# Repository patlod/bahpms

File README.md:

# bahpms

Thesis Project:  Development and Evaluation of a Hybrid Power Management System for Airships Intended for Infrared Thermographic Inspection of Photovoltaic Plants

## Airship Prototype

## Concept

### Inteded Mission
While vehcile monitors photovoltaic plants it will extend its flight time by charging itself with solar power.

## Gondola & Vehicle Control

## Hybrid Power Management System (HPMS)
Hardware which manages the charging process of the vehicle and switching between power supplies.

## Testing HPMS

## Hardware Communication Client on the Ground
### Concept

Wireless data exchange with vehicle hardware including charge states, charge rates, battery information (which is currently active and which is charged), manually switch between power supplies, etc.

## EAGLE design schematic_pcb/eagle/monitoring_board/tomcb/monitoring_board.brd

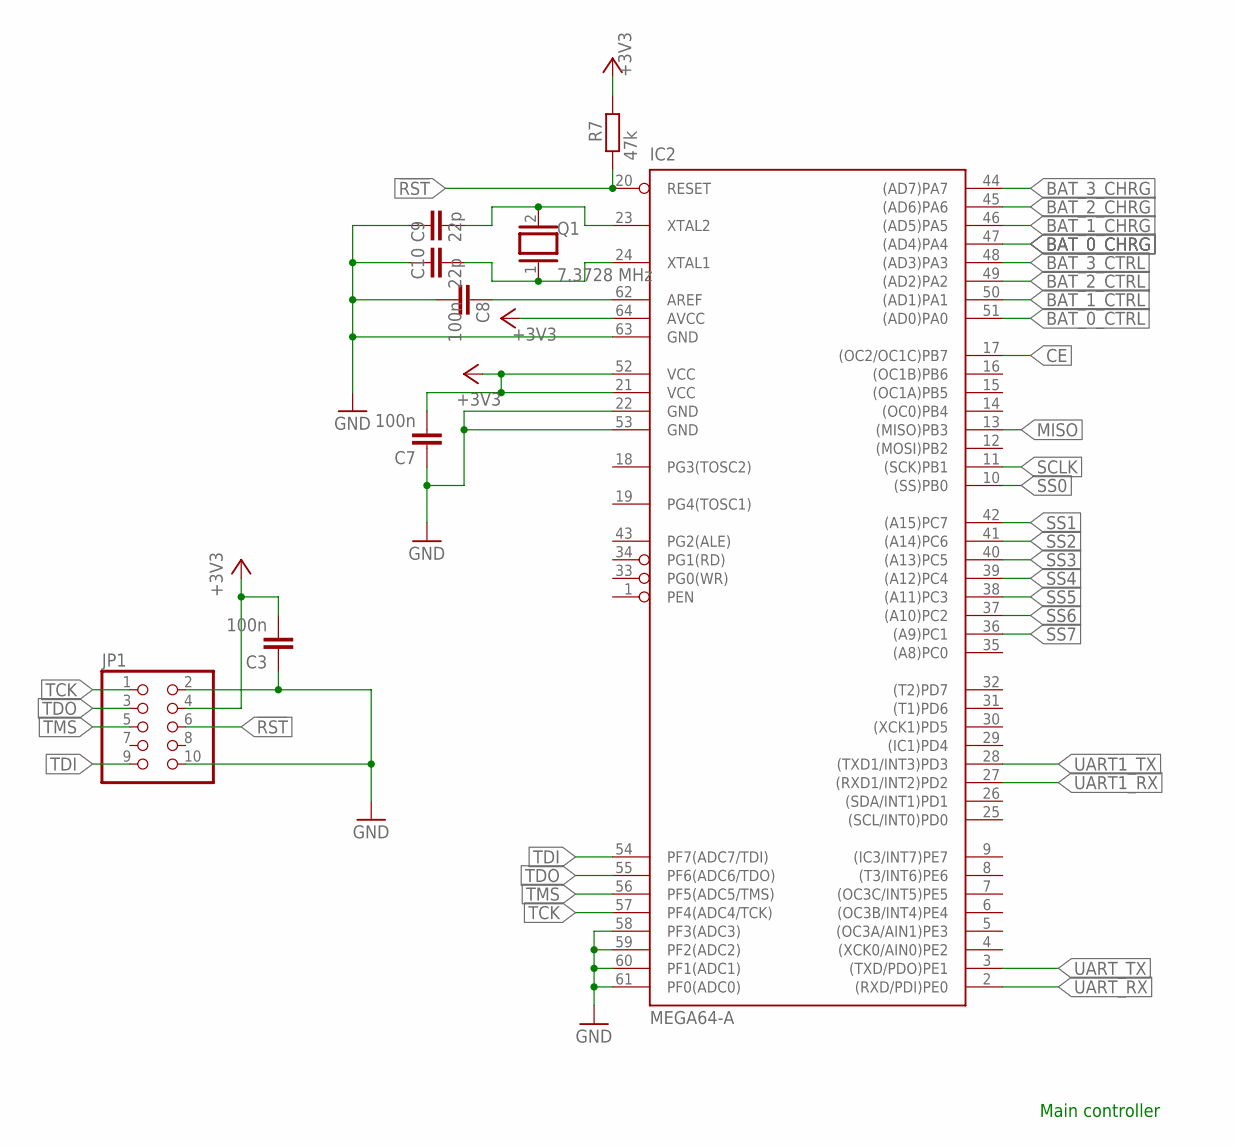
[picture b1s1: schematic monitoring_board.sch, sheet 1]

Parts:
C3, C7, C8: 100n; C0603
C9, C10: 22p; C0603
IC2: MEGA64-A; TQFP64
JP1: PINHD-2X5; 2X05
Q1: 7.3728 MHz; QS
R7: 47k; R0603

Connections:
!RST: IC2.20 (RESET), JP1.6, R7.1
AREF: C8.1, IC2.62 (AREF)
BAT_0_CHRG: IC2.47 ((AD4)PA4); also elsewhere on the board
BAT_0_CTRL: IC2.51 ((AD0)PA0); also elsewhere on the board
BAT_1_CHRG: IC2.46 ((AD5)PA5); also elsewhere on the board
BAT_1_CTRL: IC2.50 ((AD1)PA1); also elsewhere on the board
BAT_2_CHRG: IC2.45 ((AD6)PA6); also elsewhere on the board
BAT_2_CTRL: IC2.49 ((AD2)PA2); also elsewhere on the board
BAT_3_CHRG: IC2.44 ((AD7)PA7); also elsewhere on the board
BAT_3_CTRL: IC2.48 ((AD3)PA3); also elsewhere on the board
CE: IC2.17 ((OC2/OC1C)PB7); also elsewhere on the board
GND: C3.1, C7.1, C8.2, C9.1, C10.1, IC2.22 (GND), IC2.53 (GND), IC2.58 (PF3(ADC3)), IC2.59 (PF2(ADC2)), IC2.60 (PF1(ADC1)), IC2.61 (PF0(ADC0)), IC2.63 (GND), JP1.2, JP1.10; also elsewhere on the board
MISO: IC2.13 ((MISO)PB3); also elsewhere on the board
unnamed: C9.2, IC2.23 (XTAL2), Q1.2
unnamed: C10.2, IC2.24 (XTAL1), Q1.1
SCLK: IC2.11 ((SCK)PB1); also elsewhere on the board
SS0: IC2.10 ((SS)PB0); also elsewhere on the board
SS1: IC2.42 ((A15)PC7); also elsewhere on the board
SS2: IC2.41 ((A14)PC6); also elsewhere on the board
SS3: IC2.40 ((A13)PC5); also elsewhere on the board
SS4: IC2.39 ((A12)PC4); also elsewhere on the board
SS5: IC2.38 ((A11)PC3); also elsewhere on the board
SS6: IC2.37 ((A10)PC2); also elsewhere on the board
SS7: IC2.36 ((A9)PC1); also elsewhere on the board
TCK: IC2.57 (PF4(ADC4/TCK)), JP1.1
TDI: IC2.54 (PF7(ADC7/TDI)), JP1.9
TDO: IC2.55 (PF6(ADC6/TDO)), JP1.3
TMS: IC2.56 (PF5(ADC5/TMS)), JP1.5
UART1_RX: IC2.27 ((RXD1/INT2)PD2); also elsewhere on the board
UART1_TX: IC2.28 ((TXD1/INT3)PD3); also elsewhere on the board
UART_RX: IC2.2 ((RXD/PDI)PE0); also elsewhere on the board
UART_TX: IC2.3 ((TXD/PDO)PE1); also elsewhere on the board
VCC3V3: C3.2, C7.2, IC2.21 (VCC), IC2.52 (VCC), IC2.64 (AVCC), JP1.4, R7.2; also elsewhere on the board

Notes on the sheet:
Main controller

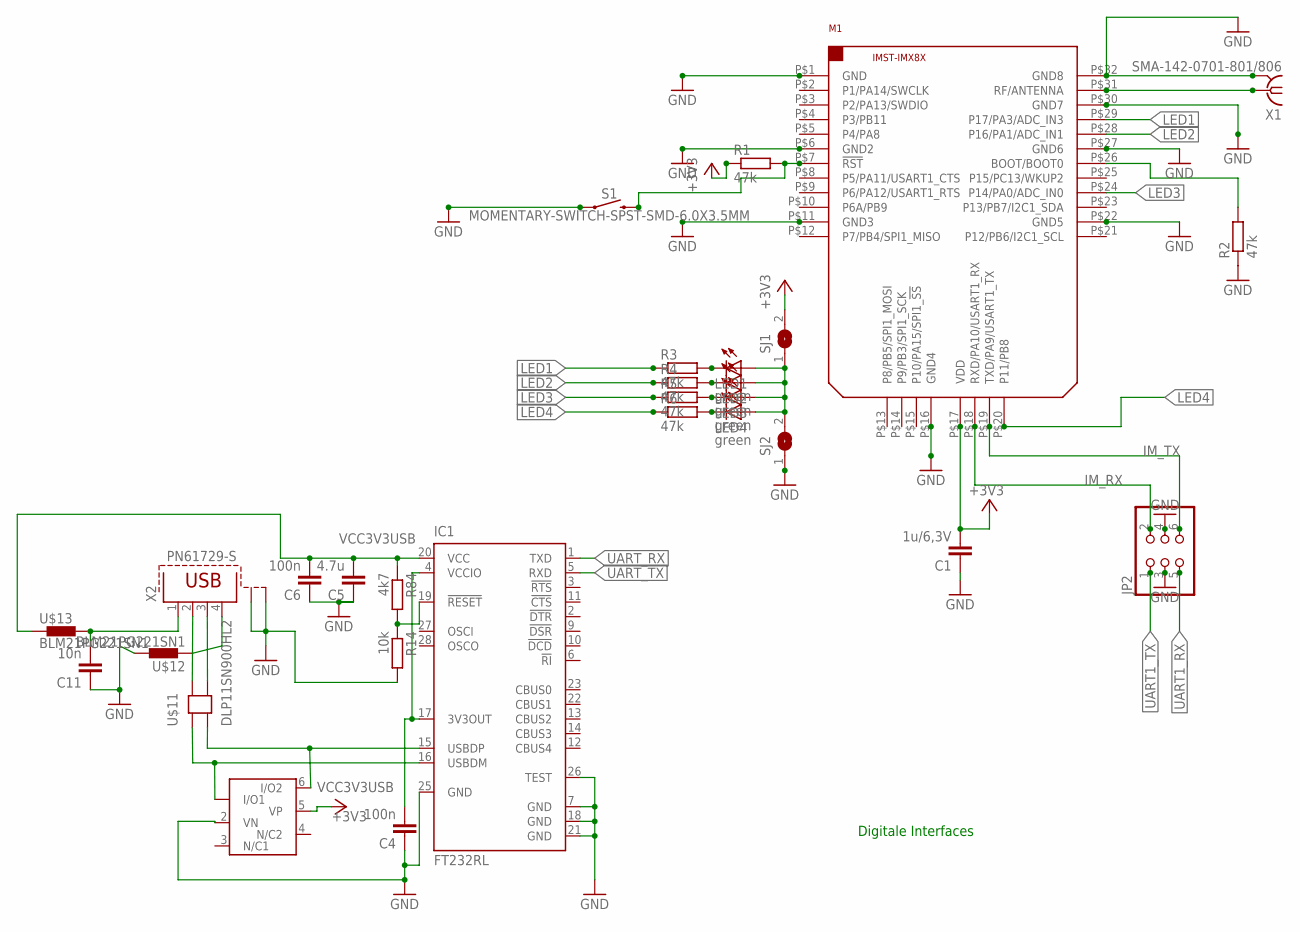
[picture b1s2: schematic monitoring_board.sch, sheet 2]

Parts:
C1: 1u/6,3V; C0603
C4, C6: 100n; C0603
C5: 4.7u; C0603
C11: 10n; C0603
IC1: FT232RL; SSOP28
JP2: PINHD-2X3; 2X03
LED1, LED2, LED3, LED4: green; CHIP-LED0603
M1: IM-X8X
R1, R2, R3, R4, R5, R6: 47k; R0603
R14: 10k; R0603
R84: 4k7; R0603
S1: MOMENTARY-SWITCH-SPST-SMD-6.0X3.5MM; TACTILE_SWITCH_SMD_6.0X3.5MM
SJ1, SJ2: SJ
U$11: DLP11SN900HL2
U$12, U$13: BLM21PG221SN1
U$14: DUP2201MR6; NUP2201MR6
X1: SMA-142-0701-801/806; J502-ND-142-0701-801/806
X2: PN61729-S

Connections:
3V3OUT: C4.2, IC1.4 (VCCIO), IC1.17 (3V3OUT)
GND: C1.1, C4.1, C5.1, C6.1, C11.1, IC1.7 (GND), IC1.18 (GND), IC1.21 (GND), IC1.25 (GND), IC1.26 (TEST), JP2.3, JP2.4, M1.P$1 (GND), M1.P$6 (GND2), M1.P$11 (GND3), M1.P$16 (GND4), M1.P$22 (GND5), M1.P$27 (GND6), M1.P$30 (GND7), M1.P$32 (GND8), R2.1, R14.2, S1.1, SJ2.1, U$12.2, U$14.2 (VN), X1.G@1 (2), X1.G@2 (2), X1.G@3 (2), X1.G@4 (2), X2.S1, X2.S2; also elsewhere on the board
IM_RX: JP2.2, M1.P$18 (RXD/PA10/USART1_RX)
IM_TX: JP2.6, M1.P$19 (TXD/PA9/USART1_TX)
LED1: M1.P$29 (P17/PA3/ADC_IN3), R3.1
LED2: M1.P$28 (P16/PA1/ADC_IN1), R4.1
LED3: M1.P$24 (P14/PA0/ADC_IN0), R5.1
LED4: M1.P$20 (P11/PB8), R6.1
unnamed: M1.P$31 (RF/ANTENNA), X1.1
unnamed: LED1.C, R3.2
unnamed: M1.P$7 (!RST), R1.2, S1.2
unnamed: M1.P$26 (BOOT/BOOT0), R2.2
unnamed: LED2.C, R4.2
unnamed: LED3.C, R5.2
unnamed: LED4.C, R6.2
unnamed: IC1.19 (!RESET), R14.1, R84.2
unnamed: LED1.A, LED2.A, LED3.A, LED4.A, SJ1.1, SJ2.2
unnamed: U$11.2, X2.2
unnamed: U$11.4, X2.3
unnamed: IC1.16 (USBDM), U$11.1, U$14.1 (I/O1)
unnamed: IC1.15 (USBDP), U$11.3, U$14.6 (I/O2)
unnamed: U$12.1, X2.4
unnamed: C11.2, U$13.2, X2.1
UART1_RX: JP2.5; also elsewhere on the board
UART1_TX: JP2.1; also elsewhere on the board
UART_RX: IC1.1 (TXD); also elsewhere on the board
UART_TX: IC1.5 (RXD); also elsewhere on the board
VCC3V3: C1.2, M1.P$17 (VDD), R1.1, SJ1.2; also elsewhere on the board
VCC3V3USB: C5.2, C6.2, IC1.20 (VCC), R84.1, U$13.1, U$14.5 (VP)

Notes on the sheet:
Digitale Interfaces

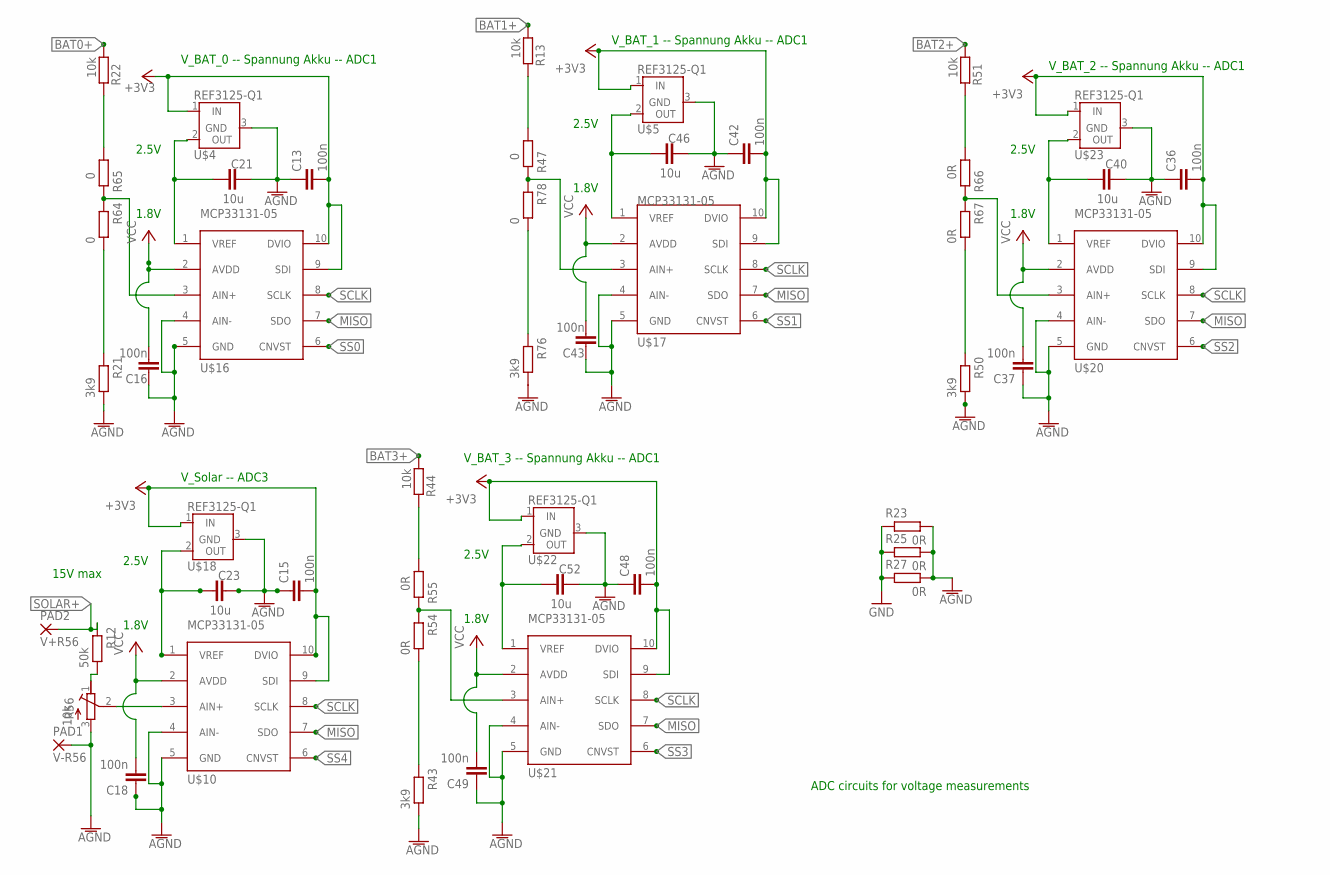
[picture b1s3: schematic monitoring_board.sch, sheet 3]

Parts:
C13, C15, C16, C18, C36, C37, C42, C43, C48, C49: 100n; C0603
C21, C23, C40, C46, C52: 10u; C0603
PAD1: V-R56; SMD1,27-2,54
PAD2: V+R56; SMD1,27-2,54
R12: 50k; R0603
R13, R22, R44, R51: 10k; R0603
R21, R43, R50, R76: 3k9; R0603
R23, R25, R27, R54, R55, R66, R67: 0R; R0603
R47, R64, R65, R78: 0; R0603
R56: 10k; RTRIMCA6
U$4, U$5, U$18, U$22, U$23: REF3125-Q1; REF31XX-Q1
U$10, U$16, U$17, U$20, U$21: MCP33131-05

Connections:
AGND: C13.1, C15.1, C16.1, C18.1, C21.2, C23.2, C36.1, C37.1, C40.2, C42.1, C43.1, C46.2, C48.1, C49.1, C52.2, PAD1.1, R21.2, R23.2, R25.2, R27.2, R43.2, R50.2, R56.3 (A), R76.2, U$4.3 (GND), U$5.3 (GND), U$10.4 (AIN-), U$10.5 (GND), U$16.4 (AIN-), U$16.5 (GND), U$17.4 (AIN-), U$17.5 (GND), U$18.3 (GND), U$20.4 (AIN-), U$20.5 (GND), U$21.4 (AIN-), U$21.5 (GND), U$22.3 (GND), U$23.3 (GND); also elsewhere on the board
BAT0+: R22.1; also elsewhere on the board
BAT1+: R13.1; also elsewhere on the board
BAT2+: R51.1; also elsewhere on the board
BAT3+: R44.1; also elsewhere on the board
GND: R23.1, R25.1, R27.1; also elsewhere on the board
MISO: U$10.7 (SDO), U$16.7 (SDO), U$17.7 (SDO), U$20.7 (SDO), U$21.7 (SDO); also elsewhere on the board
unnamed: R12.2, R56.1 (E)
unnamed: R51.2, R66.2
unnamed: C23.1, U$10.1 (VREF), U$18.2 (OUT)
unnamed: C21.1, U$4.2 (OUT), U$16.1 (VREF)
unnamed: R56.2 (S), U$10.3 (AIN+)
unnamed: R22.2, R65.2
unnamed: R21.1, R64.2
unnamed: R13.2, R47.2
unnamed: R76.1, R78.2
unnamed: R50.1, R67.2
unnamed: R44.2, R55.2
unnamed: R43.1, R54.2
unnamed: C40.1, U$20.1 (VREF), U$23.2 (OUT)
unnamed: R64.1, R65.1, U$16.3 (AIN+)
unnamed: R66.1, R67.1, U$20.3 (AIN+)
unnamed: C46.1, U$5.2 (OUT), U$17.1 (VREF)
unnamed: R47.1, R78.1, U$17.3 (AIN+)
unnamed: R54.1, R55.1, U$21.3 (AIN+)
unnamed: C52.1, U$21.1 (VREF), U$22.2 (OUT)
SCLK: U$10.8 (SCLK), U$16.8 (SCLK), U$17.8 (SCLK), U$20.8 (SCLK), U$21.8 (SCLK); also elsewhere on the board
SOLAR+: PAD2.1, R12.1; also elsewhere on the board
SS0: U$16.6 (CNVST); also elsewhere on the board
SS1: U$17.6 (CNVST); also elsewhere on the board
SS2: U$20.6 (CNVST); also elsewhere on the board
SS3: U$21.6 (CNVST); also elsewhere on the board
SS4: U$10.6 (CNVST); also elsewhere on the board
VCC1V8: C16.2, C18.2, C37.2, C43.2, C49.2, U$10.2 (AVDD), U$16.2 (AVDD), U$17.2 (AVDD), U$20.2 (AVDD), U$21.2 (AVDD); also elsewhere on the board
VCC3V3: C13.2, C15.2, C36.2, C42.2, C48.2, U$4.1 (IN), U$5.1 (IN), U$10.9 (SDI), U$10.10 (DVIO), U$16.9 (SDI), U$16.10 (DVIO), U$17.9 (SDI), U$17.10 (DVIO), U$18.1 (IN), U$20.9 (SDI), U$20.10 (DVIO), U$21.9 (SDI), U$21.10 (DVIO), U$22.1 (IN), U$23.1 (IN); also elsewhere on the board

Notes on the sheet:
1.8V
2.5V
V_BAT_0 -- Spannung Akku -- ADC1
ADC circuits for voltage measurements
V_BAT_2 -- Spannung Akku -- ADC1
V_BAT_1 -- Spannung Akku -- ADC1
V_BAT_3 -- Spannung Akku -- ADC1
V_Solar -- ADC3
15V max

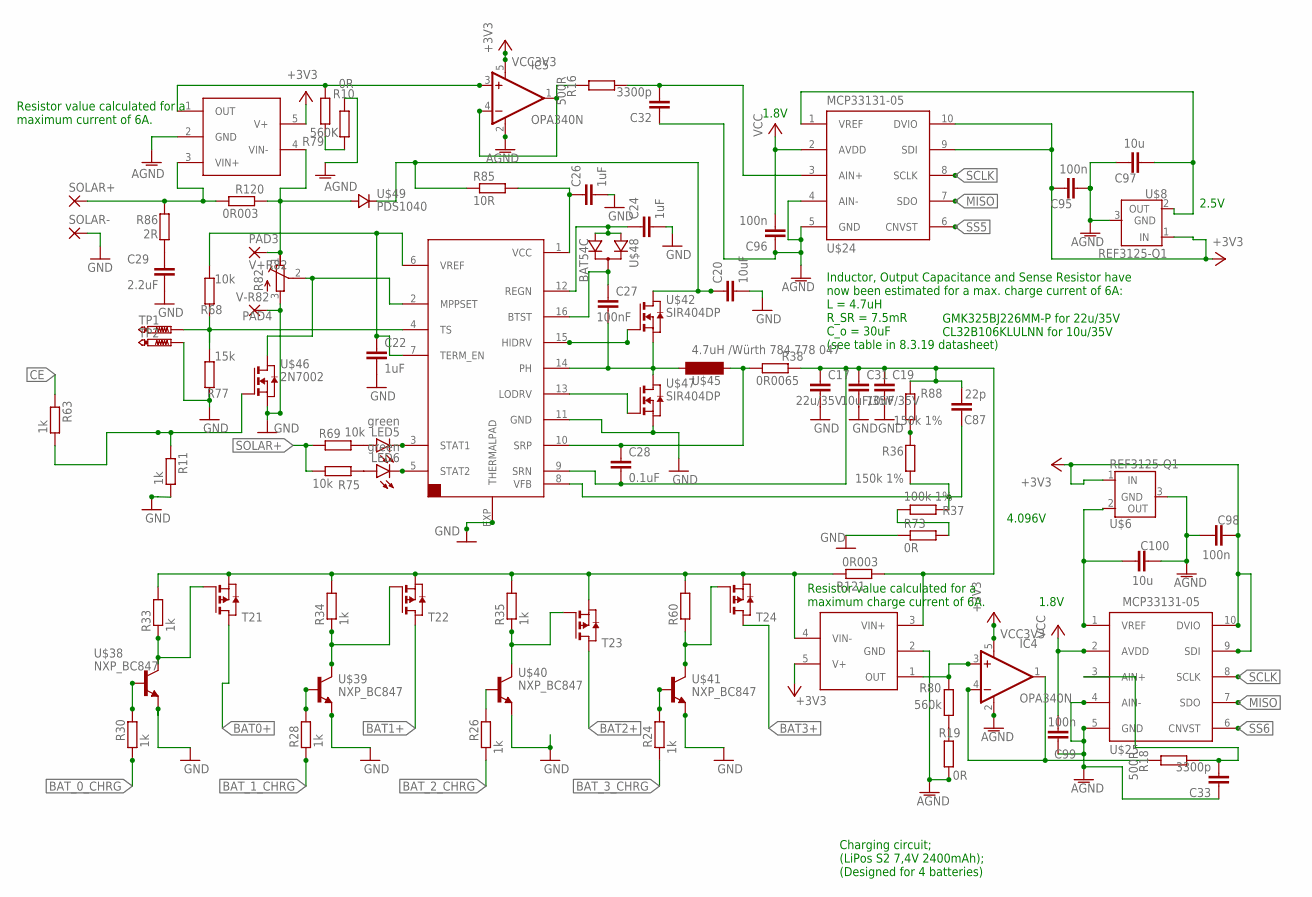
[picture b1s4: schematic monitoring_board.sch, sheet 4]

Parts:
C17: 22u/35V; C1210
C19, C31: 10uF/35V; C1210
C20: 10uF; C1210
C22, C24, C26: 1uF; C0805
C27: 100nF; C0805
C28: 0.1uF; C0603K
C29: 2.2uF; C0805
C32, C33: 3300p; C0603
C87: 22p; C0603
C95, C96, C98, C99: 100n; C0603
C97, C100: 10u; C0603
IC4, IC5: OPA340N; SOT23-5
LED5, LED6: green; CHIPLED_0603
PAD3: V+R82; SMD1,27-2,54
PAD4: V-R82; SMD1,27-2,54
R10, R19: 0R; R0603
R11, R24, R26, R28, R30, R33, R34, R35, R60, R63: 1k; R0603
R16, R18: 500R; R0603
R36, R88: 150k 1%; R0402
R37: 100k 1%; R0402
R38: 0R0065; R2512
R68, R69, R75: 10k; R0402
R73: 0R; R0402
R77: 15k; R0402
R79: 560K; R0603
R80: 560k; R0603
R82: R-TRIMM; RTRIMCA6
R85: 10R; R1206
R86: 2R; R2012
R120, R121: 0R003; R2512
SOLAR+: SMDPAD
SOLAR-: SMDPAD
T21, T22, T23, T24: SI7157DP
TP1, TP2: PTR1PAD1-13; P1-13
U$6, U$8: REF3125-Q1; REF31XX-Q1
U$24, U$25: MCP33131-05
U$27, U$28: INA138
U$36: BQ24650
U$38, U$39, U$40, U$41: NXP_BC847
U$42, U$47: SIR404DP
U$45: 4.7uH /Würth 784 778 047; IHLP-2525CZ-01
U$46: 2N7002
U$48: BAT54C
U$49: PDS1040

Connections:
AGND: C32.1, C33.1, C95.1, C96.1, C97.2, C98.1, C99.1, C100.2, IC4.2 (V-), IC5.2 (V-), R10.1, R19.1, U$6.3 (GND), U$8.3 (GND), U$24.4 (AIN-), U$24.5 (GND), U$25.4 (AIN-), U$25.5 (GND), U$27.2 (GND), U$28.2 (GND); also elsewhere on the board
AIN+: IC4.3 (+IN), R80.2, U$27.1 (OUT)
BAT0+: T21.5 (D), T21.6 (D), T21.7 (D), T21.8 (D), T21.9 (D); also elsewhere on the board
BAT1+: T22.5 (D), T22.6 (D), T22.7 (D), T22.8 (D), T22.9 (D); also elsewhere on the board
BAT2+: T23.5 (D), T23.6 (D), T23.7 (D), T23.8 (D), T23.9 (D); also elsewhere on the board
BAT3+: T24.5 (D), T24.6 (D), T24.7 (D), T24.8 (D), T24.9 (D); also elsewhere on the board
BAT_0_CHRG: R30.1; also elsewhere on the board
BAT_1_CHRG: R28.1; also elsewhere on the board
BAT_2_CHRG: R26.1; also elsewhere on the board
BAT_3_CHRG: R24.1; also elsewhere on the board
BTST: C27.1, U$36.16 (BTST), U$48.3 (C)
CE: R63.2; also elsewhere on the board
GND: C17.2, C19.2, C20.2, C22.2, C24.2, C26.2, C29.2, C31.2, PAD4.1, R11.1, R73.1, R77.1, R82.3 (A), SOLAR-.1, TP2.TP, U$36.11 (GND), U$36.EXP (THERMALPAD), U$38.2 (E), U$39.2 (E), U$40.2 (E), U$41.2 (E), U$46.2 (S), U$47.1 (S), U$47.2 (S), U$47.3 (S); also elsewhere on the board
HIDRV: U$36.15 (HIDRV), U$42.4 (G)
LODRV: U$36.13 (LODRV), U$47.4 (G)
MISO: U$24.7 (SDO), U$25.7 (SDO); also elsewhere on the board
MPPSET: R82.2 (S), U$36.2 (MPPSET), U$46.3 (D)
unnamed: IC4.1 (OUT), IC4.4 (-IN), R18.1
unnamed: IC5.1 (OUT), IC5.4 (-IN), R16.1
unnamed: R33.1, T21.4 (G), U$38.3 (C)
unnamed: C32.2, R16.2, U$24.3 (AIN+)
unnamed: C33.2, R18.2, U$25.3 (AIN+)
unnamed: IC5.3 (+IN), R79.2, U$28.1 (OUT)
unnamed: R34.1, T22.4 (G), U$39.3 (C)
unnamed: LED5.A, R69.2
unnamed: R35.1, T23.4 (G), U$40.3 (C)
unnamed: LED6.A, R75.2
unnamed: C29.1, R86.1
unnamed: R10.2, R79.1
unnamed: R60.1, T24.4 (G), U$41.3 (C)
unnamed: R26.2, U$40.1 (B)
unnamed: R28.2, U$39.1 (B)
unnamed: R30.2, U$38.1 (B)
unnamed: R24.2, U$41.1 (B)
unnamed: R11.2, R63.1, U$46.1 (G)
unnamed: R36.2, R88.1
unnamed: R19.2, R80.1
unnamed: C87.1, R36.1, R37.2, U$36.8 (VFB)
unnamed: R37.1, R73.2
unnamed: C26.1, R85.2, U$36.1 (VCC)
unnamed: C20.1, R85.1, U$42.5 (D), U$42.6 (D), U$42.7 (D), U$42.8 (D), U$42.9 (D), U$49.P$1 (C)
unnamed: PAD3.1, R82.1 (E), R120.2, U$28.4 (VIN-), U$49.1 (A), U$49.2 (A)
unnamed: C100.1, U$6.2 (OUT), U$25.1 (VREF)
unnamed: R33.2, R34.2, R35.2, R60.2, R121.2, T21.1 (S), T21.2 (S), T21.3 (S), T22.1 (S), T22.2 (S), T22.3 (S), T23.1 (S), T23.2 (S), T23.3 (S), T24.1 (S), T24.2 (S), T24.3 (S), U$27.4 (VIN-)
unnamed: C97.1, U$8.2 (OUT), U$24.1 (VREF)
PH: C27.2, U$36.14 (PH), U$42.1 (S), U$42.2 (S), U$42.3 (S), U$45.1, U$47.5 (D), U$47.6 (D), U$47.7 (D), U$47.8 (D), U$47.9 (D)
REGN: C24.1, U$36.12 (REGN), U$48.1 (A1), U$48.2 (A2)
SCLK: U$24.8 (SCLK), U$25.8 (SCLK); also elsewhere on the board
SOLAR+: R69.1, R75.1, R86.2, R120.1, SOLAR+.1, U$28.3 (VIN+); also elsewhere on the board
SRN: C17.1, C19.1, C28.2, C31.1, C87.2, R38.2, R88.2, R121.1, U$27.3 (VIN+), U$36.9 (SRN)
SRP: C28.1, R38.1, U$36.10 (SRP), U$45.2
SS5: U$24.6 (CNVST); also elsewhere on the board
SS6: U$25.6 (CNVST); also elsewhere on the board
STAT1: LED5.C, U$36.3 (STAT1)
STAT2: LED6.C, U$36.5 (STAT2)
TS: R68.1, R77.2, TP1.TP, U$36.4 (TS)
VCC1V8: C96.2, C99.2, U$24.2 (AVDD), U$25.2 (AVDD); also elsewhere on the board
VCC3V3: C95.2, C98.2, IC4.5 (V+), IC5.5 (V+), U$6.1 (IN), U$8.1 (IN), U$24.9 (SDI), U$24.10 (DVIO), U$25.9 (SDI), U$25.10 (DVIO), U$27.5 (V+), U$28.5 (V+); also elsewhere on the board
VREF: C22.1, R68.2, U$36.6 (VREF), U$36.7 (TERM_EN)

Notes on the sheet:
Charging circuit; (LiPos S2 7,4V 2400mAh); (Designed for 4 batteries)
1.8V
4.096V
2.5V
Inductor, Output Capacitance and Sense Resistor have now been estimated for a max. charge current of 6A: L = 4.7uH R_SR = 7.5mR C_o = 30uF (see table in 8.3.19 datasheet)
Resistor value calculated for a maximum charge current of 6A.
Resistor value calculated for a maximum current of 6A.
GMK325BJ226MM-P for 22u/35V CL32B106KLULNN for 10u/35V

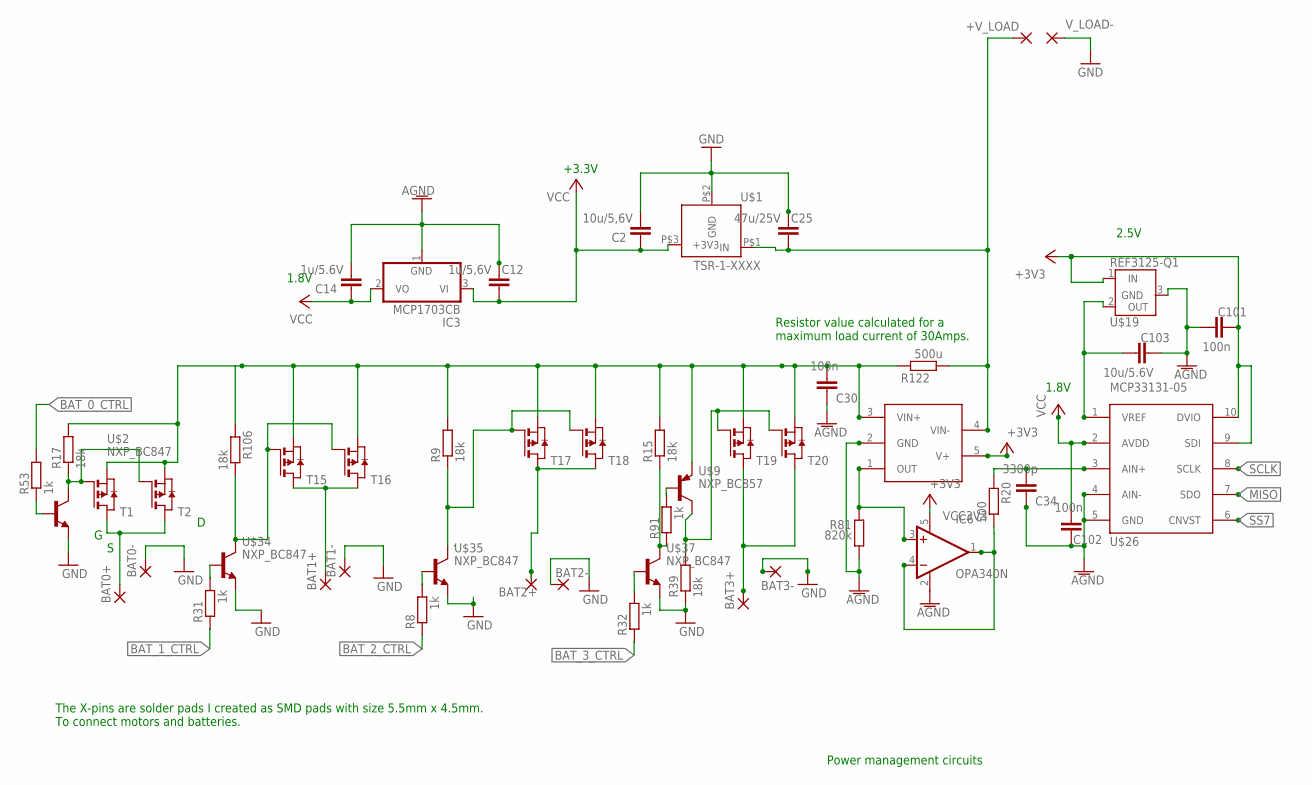
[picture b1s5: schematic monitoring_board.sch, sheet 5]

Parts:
+V_LOAD: SMDPAD
BAT0+, BAT0-, BAT1+, BAT1-, BAT2+, BAT2-, BAT3+, BAT3-: SMDPAD
C2: 10u/5,6V; C1206
C12: 1u/5,6V; C1206
C14: 1u/5.6V; C1206
C25: 47u/25V; C1206
C30, C101, C102: 100n; C0603
C34: 3300p; C0603
C103: 10u/5.6V; C0603
IC3: MCP1703CB; SOT23
IC6: OPA340N; SOT23-5
R8, R31, R32, R53, R91: 1k; R0603
R9, R15, R17, R39, R106: 18k; R0603
R20: 500; R0603
R81: 820k; R0603
R122: 500u; R2512
T1, T2, T15, T16, T17, T18, T19, T20: SI7157DP
U$1: TSR-1-XXXX
U$2, U$34, U$35, U$37: NXP_BC847
U$9: NXP_BC857
U$19: REF3125-Q1; REF31XX-Q1
U$26: MCP33131-05
U$29: INA138
V_LOAD-: SMDPAD

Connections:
+V_LOAD: +V_LOAD.1, C25.1, R122.1, U$1.P$1 (IN), U$29.4 (VIN-)
-V_LOAD: C30.2, R9.2, R15.2, R17.2, R106.2, R122.2, T1.1 (S), T1.2 (S), T1.3 (S), T2.1 (S), T2.2 (S), T2.3 (S), T15.1 (S), T15.2 (S), T15.3 (S), T16.1 (S), T16.2 (S), T16.3 (S), T17.1 (S), T17.2 (S), T17.3 (S), T18.1 (S), T18.2 (S), T18.3 (S), T19.1 (S), T19.2 (S), T19.3 (S), T20.1 (S), T20.2 (S), T20.3 (S), U$9.2 (E), U$29.3 (VIN+)
AGND: C12.2, C14.2, C30.1, C34.1, C101.1, C102.1, C103.2, IC3.1 (GND), IC6.2 (V-), R81.1, U$19.3 (GND), U$26.4 (AIN-), U$26.5 (GND), U$29.2 (GND); also elsewhere on the board
BAT0+: BAT0+.1, T1.5 (D), T1.6 (D), T1.7 (D), T1.8 (D), T1.9 (D), T2.5 (D), T2.6 (D), T2.7 (D), T2.8 (D), T2.9 (D); also elsewhere on the board
BAT1+: BAT1+.1, T15.5 (D), T15.6 (D), T15.7 (D), T15.8 (D), T15.9 (D), T16.5 (D), T16.6 (D), T16.7 (D), T16.8 (D), T16.9 (D); also elsewhere on the board
BAT2+: BAT2+.1, T17.5 (D), T17.6 (D), T17.7 (D), T17.8 (D), T17.9 (D), T18.5 (D), T18.6 (D), T18.7 (D), T18.8 (D), T18.9 (D); also elsewhere on the board
BAT3+: BAT3+.1, T19.5 (D), T19.6 (D), T19.7 (D), T19.8 (D), T19.9 (D), T20.5 (D), T20.6 (D), T20.7 (D), T20.8 (D), T20.9 (D); also elsewhere on the board
BAT_0_CTRL: R53.2; also elsewhere on the board
BAT_1_CTRL: R31.2; also elsewhere on the board
BAT_2_CTRL: R8.2; also elsewhere on the board
BAT_3_CTRL: R32.2; also elsewhere on the board
GND: BAT0-.1, BAT1-.1, BAT2-.1, BAT3-.1, C2.2, C25.2, R39.1, U$1.P$2 (GND), U$2.2 (E), U$34.2 (E), U$35.2 (E), U$37.2 (E), V_LOAD-.1; also elsewhere on the board
MISO: U$26.7 (SDO); also elsewhere on the board
unnamed: R106.1, T15.4 (G), T16.4 (G), U$34.3 (C)
unnamed: R9.1, T17.4 (G), T18.4 (G), U$35.3 (C)
unnamed: R91.1, U$9.1 (B)
unnamed: R8.1, U$35.1 (B)
unnamed: IC6.3 (+IN), R81.2, U$29.1 (OUT)
unnamed: R32.1, U$37.1 (B)
unnamed: R17.1, T1.4 (G), T2.4 (G), U$2.3 (C)
unnamed: IC6.1 (OUT), IC6.4 (-IN), R20.1
unnamed: R53.1, U$2.1 (B)
unnamed: R31.1, U$34.1 (B)
unnamed: R39.2, T19.4 (G), T20.4 (G), U$9.3 (C)
unnamed: C34.2, R20.2, U$26.3 (AIN+)
unnamed: R15.1, R91.2, U$37.3 (C)
unnamed: C103.1, U$19.2 (OUT), U$26.1 (VREF)
SCLK: U$26.8 (SCLK); also elsewhere on the board
SS7: U$26.6 (CNVST); also elsewhere on the board
VCC1V8: C14.1, C102.2, IC3.2 (VO), U$26.2 (AVDD); also elsewhere on the board
VCC3V3: C2.1, C12.1, C101.2, IC3.3 (VI), IC6.5 (V+), U$1.P$3 (+3V3), U$19.1 (IN), U$26.9 (SDI), U$26.10 (DVIO), U$29.5 (V+); also elsewhere on the board

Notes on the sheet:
1.8V
Power management circuits
+3.3V
Resistor value calculated for a maximum load current of 30Amps.
The X-pins are solder pads I created as SMD pads with size 5.5mm x 4.5mm. To connect motors and batteries.
2.5V

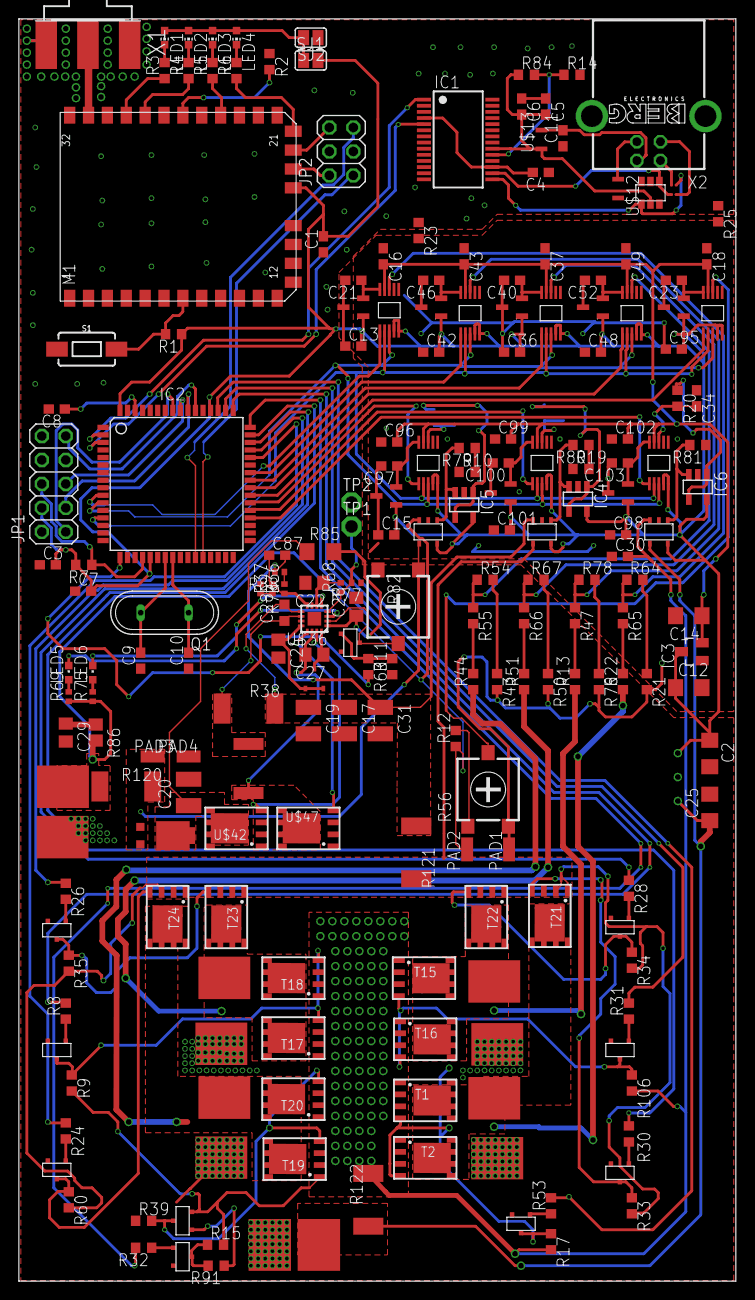
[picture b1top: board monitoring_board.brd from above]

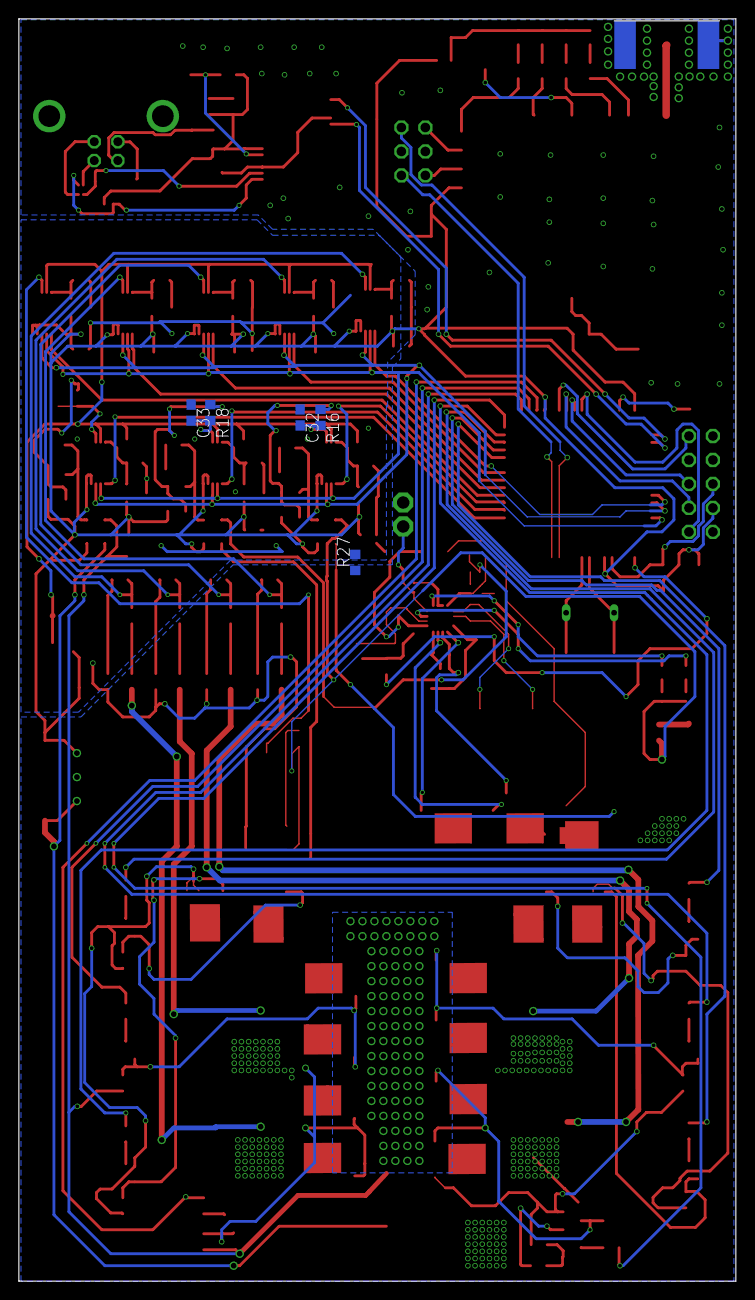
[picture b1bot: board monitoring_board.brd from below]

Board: 2 copper layers, 76.0 x 133.8 mm, 217 parts (5 on the bottom side), 139 nets.

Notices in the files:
parts and their libraries:
SparkFun-Switches: Licensing: Creative Commons ShareAlike 4.0 International - https://creativecommons.org/licenses/by-sa/4.0
